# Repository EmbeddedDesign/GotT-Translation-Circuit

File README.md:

# GotT Translation Circuit 

GotT is a Bluetooth voice modulator circuit for Daleks

## FAQ

### GotT?

["gift of the Time Lord" or "gift of the TARDIS"](http://tardis.wikia.com/wiki/Translation_circuit) depending upon whether you're a Tom Baker or Christopher Eccleston fan respectively.

### What is a "voice modulator"?

A voice modulator is device for altering (or [modulating](https://en.wikipedia.org/wiki/Modulation)) the sound of one's voice.

In the context of Daleks, this usually refers to [ring modulation](https://en.wikipedia.org/wiki/Ring_modulation), whereby two signals mixed (i.e. - multiplied, or [Heterodyned](https://en.wikipedia.org/wiki/Heterodyne)). The first of these signals is typically a voice and the second is often a [sine wave](https://en.wikipedia.org/wiki/Sine_wave) at a frequency of about 30Hz.

This was originally accomplished through the use of a [Moog Ring Modulator similar to this](http://www.moogmusic.com/products/moogerfoogers/mf-102-ring-modulator).

While purists may argue that nothing sounds quite like a pair of audio transformers connected by a ring of four Germanium diodes (which is where the "ring" in "ring modulator" comes from), like the original Moog, GotT accomplishes this task in software.

GotT is a modern modulator for modern Daleks.

## The Board

### Schematic

All of the design files for the board can be found in the [/Electrical/](https://github.com/EmbeddedDesign/GotT-Translation-Circuit/tree/master/Electrical) subdirectory of this repository.

## Test Boards

Several of the sub-circuits on the GotT including those of the lights, PWM isolator, power, and WT32i were first constructed at test boards to ensure proper concept and functionality prior to integration into the larger design.

A detailed overview of the test boards and deeper descriptions of basic functionality [can be found here](https://noctivore.com/2016/06/12/gott-translation-circuit/).

Images of the schematics and layout along with complete deign files and BOM for each of the test boards can be found in the respective subdirectories of the [/Electrical/Test Boards/](https://github.com/EmbeddedDesign/GotT-Translation-Circuit/tree/master/Electrical/Test%20Boards) section of this repository.

## License

[MIT License](LICENSE) © [Operator](https://github.com/EmbeddedDesign)

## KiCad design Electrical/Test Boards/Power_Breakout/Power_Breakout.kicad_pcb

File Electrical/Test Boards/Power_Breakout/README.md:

# Power Test Board Breakout

## Schematic

## Layout

## License

[MIT License](LICENSE) © [Operator](https://github.com/EmbeddedDesign)

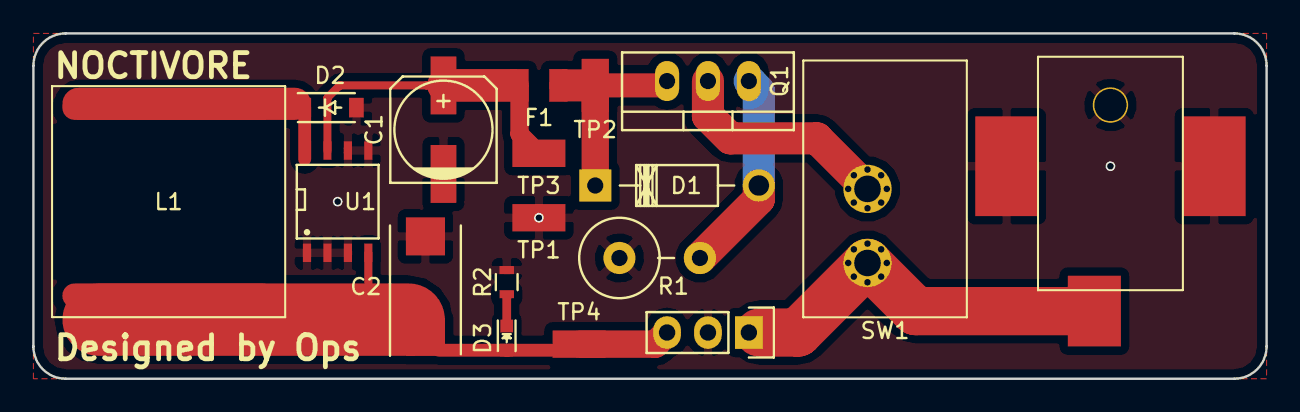
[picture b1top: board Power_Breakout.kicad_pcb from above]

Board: 2 copper layers, 76.6 x 21.5 mm, 18 parts (0 on the bottom side), 9 nets.

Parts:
C1: 68uF; c_elec_6.3x7.7
C2: 10uF; TantalC_SizeD_EIA-7343_Reflow
CON1: BARREL_JACK; PJ-036AH-SMT-TR_Barrel_Jack
D1: 1N4749A; Diode_DO-41_SOD81_Horizontal_RM10
D2: MBRS130L; SOD-123
D3: PWR LED; LED_0603
F1: 0ZCJ0050AF2E; Fuse_SMD1206_Reflow
L1: 100uH; PE-53820SNL_Pulse_Inductor
P1: Header; Pin_Header_Straight_1x03
Q1: FQP47P06; TO-220_Neutral123_Vertical
R1: 100K; Resistor_Vertical_RM5mm
R2: 100; R_0603
SW1: GF-123-0054
TP1, TP2, TP3, TP4: TP1; RCS-0C_Test_Point
U1: LM2594; SOIC-8-N

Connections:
+3V3: C2.1, D3.2, L1.2, P1.3, TP4.1, U1.4
/VIN: CON1.1, P1.1, SW1.1
GND: C1.2, C2.2, CON1.2, CON1.3, D2.2, P1.2, R1.1, R2.2, TP1.1, U1.1, U1.2, U1.3, U1.5, U1.6
unnamed: C1.1, F1.2, TP3.1, U1.7
unnamed: D1.1, F1.1, Q1.3, TP2.1
unnamed: D1.2, Q1.1, R1.2
unnamed: D2.1, L1.1, U1.8
unnamed: D3.1, R2.1
unnamed: Q1.2, SW1.2

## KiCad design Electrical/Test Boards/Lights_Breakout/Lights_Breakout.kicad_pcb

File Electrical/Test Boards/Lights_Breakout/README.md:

# Lights Test Board Breakout

## Schematic

## Layout

## License

[MIT License](LICENSE) © [Operator](https://github.com/EmbeddedDesign)

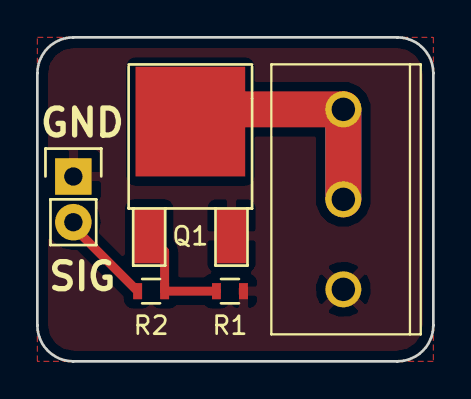
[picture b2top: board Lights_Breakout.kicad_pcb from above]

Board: 2 copper layers, 22.0 x 18.0 mm, 5 parts (0 on the bottom side), 4 nets.

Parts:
P1: LIGHTS_HEADER; 1935174_Phoenix_Contact_01X03
P2: SIGNAL_HEADER; Socket_Strip_Straight_1x02
Q1: IPD30N06S2L-23; TO-252-2Lead
R1: 10K; R_0603
R2: 100; R_0603

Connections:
GND: P1.1, P2.1, Q1.3, R1.1
unnamed: P1.2, P1.3, Q1.2
unnamed: P2.2, R2.2
unnamed: Q1.1, R1.2, R2.1

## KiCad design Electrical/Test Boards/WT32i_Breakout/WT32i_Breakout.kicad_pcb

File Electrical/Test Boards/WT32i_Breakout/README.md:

# WT32i Test Board Breakout

## Schematic

## Layout

## License

[MIT License](LICENSE) © [Operator](https://github.com/EmbeddedDesign)

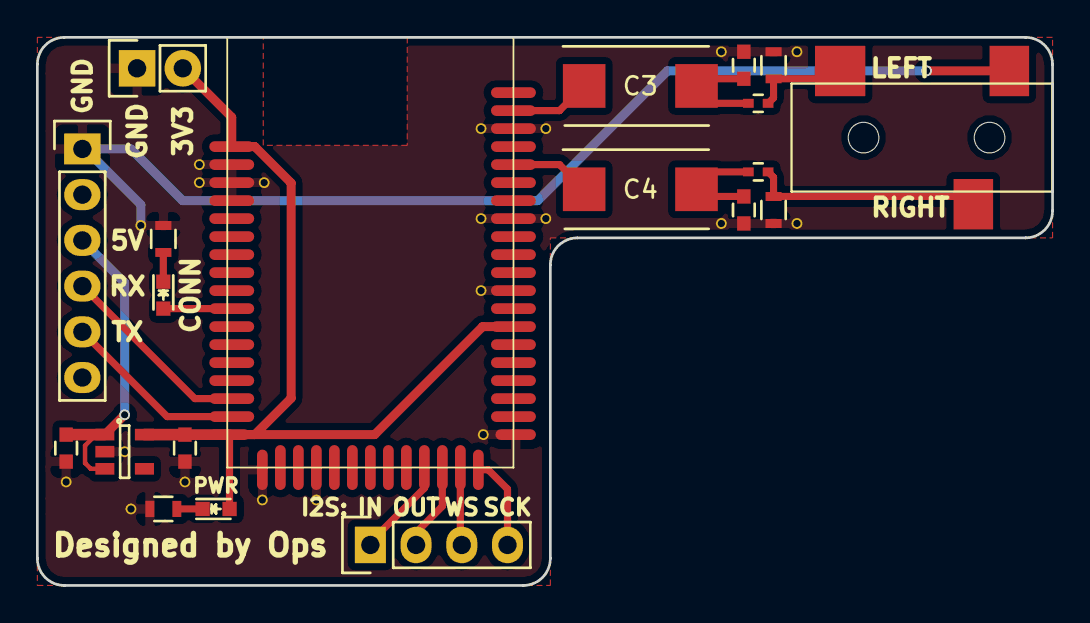
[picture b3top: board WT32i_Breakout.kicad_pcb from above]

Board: 2 copper layers, 56.4 x 30.5 mm, 20 parts (0 on the bottom side), 18 nets.

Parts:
C1, C2: 2.2uF; C_0603
C3, C4: 330uF/6.3V; TantalC_SizeD_EIA-7343_Reflow
C5, C6: 33pF; C_0603
D2: CONN_LED; LED_0603
D3: PWR_LED; LED_0603
L1, L2: 33nH; C_0402
P1: UART_CONN; Socket_Strip_Straight_1x06
P2: I2S_CONN; Socket_Strip_Straight_1x04
P3: PWR_CONN; Socket_Strip_Straight_1x02
P4: Stereo_Audio_Jack_3.5mm; CUI_Stereo_Audio_Jack
R1: 100; R_0603
R2: 820; R_0603
R3, R4: 1M; R_0603
U1: WT32i
U2: TPS79933; SOT-23-5

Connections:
+3V3: C2.1, D3.2, P3.2, U1.1, U1.17, U1.37, U2.5
+5V: C1.1, P1.3, U2.1, U2.3
/I2S_IN: P2.1, U1.27
/I2S_OUT: P2.2, U1.28
/I2S_SCK: P2.4, U1.30
/I2S_WS: P2.3, U1.29
/UART_RXD: P1.4, U1.15
/UART_TXD: P1.5, U1.16
GND: C1.2, C2.2, C5.2, C6.1, P1.1, P3.1, R1.2, R2.2, R3.1, R4.2, U1.2, U1.3, U1.4, U1.18, U1.21, U1.31, U1.39, U1.43, U1.48, U2.2
unnamed: C3.1, U1.49
unnamed: C3.2, C6.2, L1.1
unnamed: C4.1, U1.46
unnamed: C4.2, C5.1, L2.2
unnamed: D2.1, R1.1
unnamed: D2.2, U1.10
unnamed: D3.1, R2.1
unnamed: L1.2, P4.2, R3.2
unnamed: L2.1, P4.3, R4.1

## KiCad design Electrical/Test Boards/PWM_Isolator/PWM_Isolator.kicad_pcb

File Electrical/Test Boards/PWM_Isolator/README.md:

# PWM Isolator Test Board Breakout

## Schematic

## Layout

## License

[MIT License](LICENSE) © [Operator](https://github.com/EmbeddedDesign)

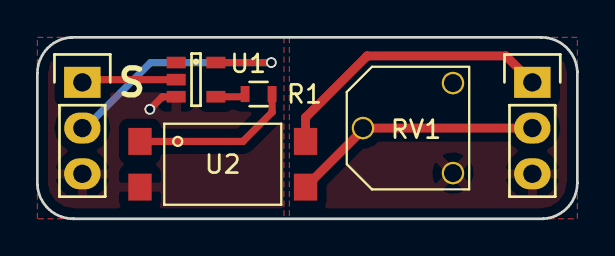
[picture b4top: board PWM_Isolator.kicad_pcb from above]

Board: 2 copper layers, 30.0 x 10.1 mm, 6 parts (0 on the bottom side), 8 nets.

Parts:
P1: RC_HEADER; Pin_Header_Straight_1x03
P2: OUT_HEADER; Pin_Header_Straight_1x03
R1: 220; R_0603
RV1: 10K; 3306F-1-103_Trim_Pot
U1: SN74LVC1G34; SOT-23-5
U2: FOD817D3SD; FOD817D3SD_Optocoupler

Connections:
+3V3: P2.1, U2.4
+5V: P1.2, U1.5
GND: P2.3, RV1.1
GNDD: P1.3, U1.3, U2.2
unnamed: P1.1, U1.2
unnamed: P2.2, RV1.2, U2.3
unnamed: R1.1, U2.1
unnamed: R1.2, U1.4

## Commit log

2016-05-26 README update
2016-05-26 Documentation update
2016-05-26 Create KiCad project
2016-05-27 add parts, footprints, docs, schems
2016-05-31 .gitignore update
2016-05-31 BOM update
2016-05-31 schematic update
2016-06-02 Add WT32i test board
2016-06-03 Test board updates
2016-06-04 Add PWM Isolator test board
2016-06-08 Power test board updates
2016-06-11 PWM isolator updates
2016-06-11 Add lights breakout board
2016-06-11 README updates
2016-06-12 Gerber generation
2016-06-12 Add schem/layout images
2016-06-12 Add test board README
2016-06-12 Add test board schems/layouts
2016-06-13 WT32i test board updates
2016-06-16 png optimization
2016-06-20 png optimization, move BOM
2016-06-20 Add WT32i layout image
2016-06-22 gerber/README updates
2016-06-23 Gerber/BOM updates
2016-07-07 Add WT32i datasheet
2016-07-09 Power test board corrections
2016-07-10 Lights test board corrections
2016-09-04 LICENSE/README update
2016-09-04 Schematic, documentation update
2016-09-04 Combine sub-circuits, update BOM/lib, add PDFs
2017-11-26 schematic updates
